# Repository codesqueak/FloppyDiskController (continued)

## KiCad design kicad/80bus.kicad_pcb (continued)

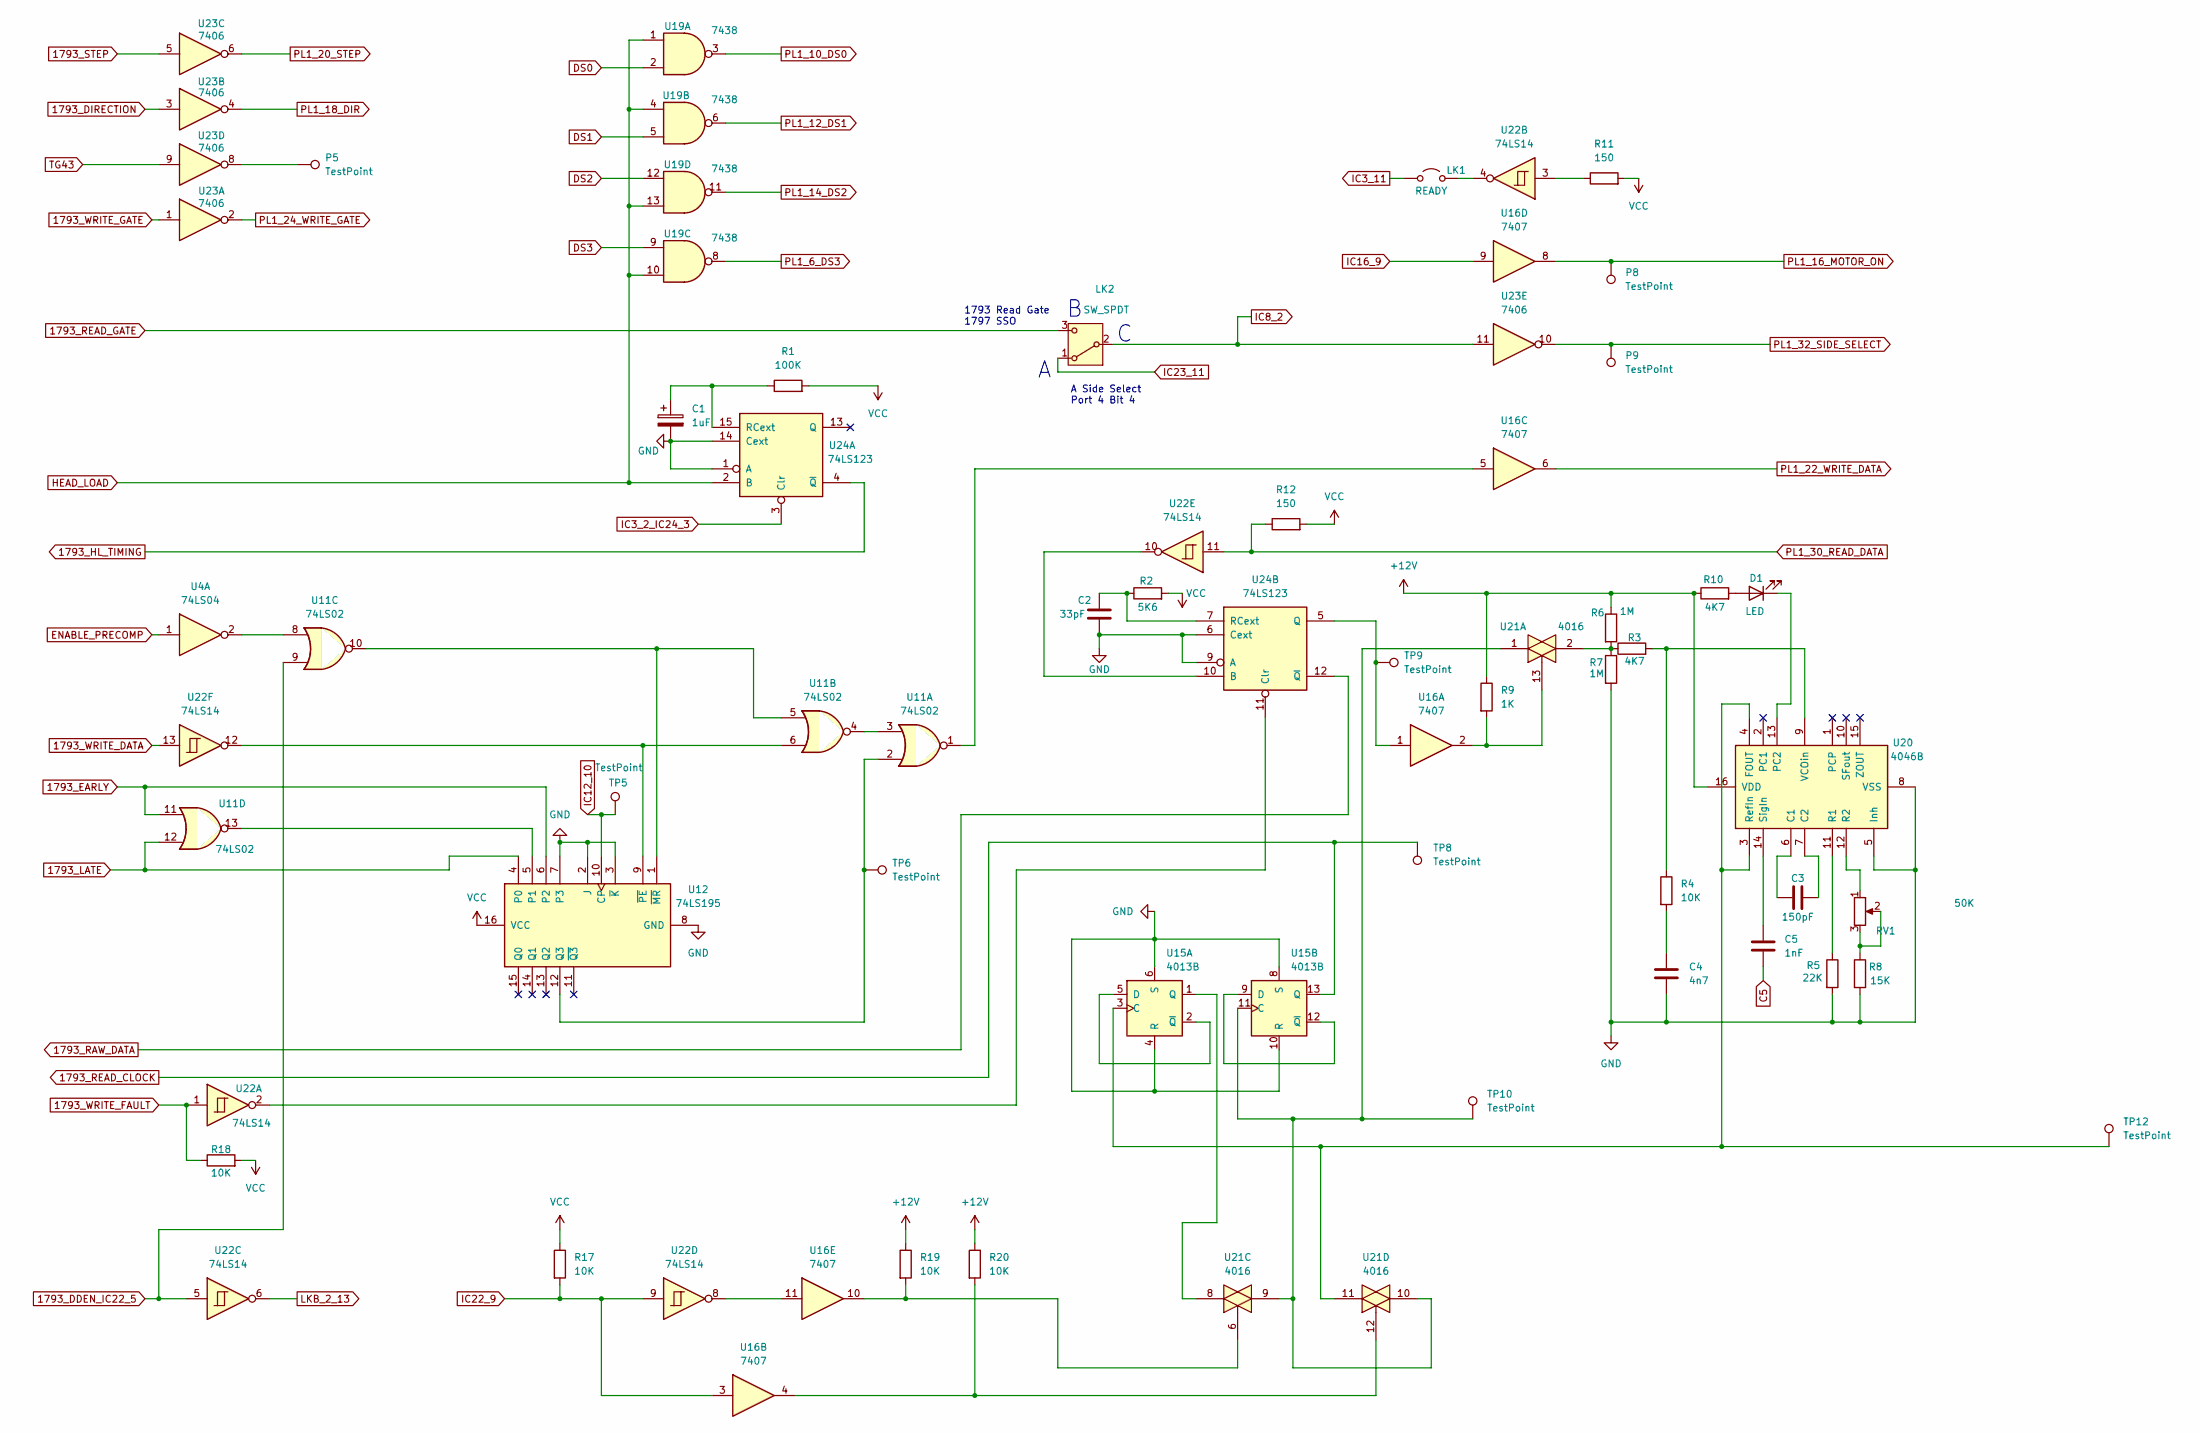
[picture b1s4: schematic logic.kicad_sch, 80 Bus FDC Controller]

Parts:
C1: 1uF; C_Disc_D6.0mm_W4.4mm_P5.00mm
C2: 33pF; C_Disc_D6.0mm_W4.4mm_P5.00mm
C3: 150pF; C_Disc_D6.0mm_W4.4mm_P5.00mm
C4: 4n7; C_Axial_L12.0mm_D6.5mm_P15.00mm_Horizontal
C5: 1nF; C_Disc_D6.0mm_W4.4mm_P5.00mm
D1: LED; LED_D3.0mm
LK1: READY; SW_DIP_SPSTx01_Slide_6.7x4.1mm_W7.62mm_P2.54mm_LowProfile
LK2: SW_SPDT; PinHeader_1x03_P2.54mm_Vertical
P5, P8, P9: TestPoint; TestPoint_THTPad_D1.5mm_Drill0.7mm
R1: 100K; R_Axial_DIN0309_L9.0mm_D3.2mm_P12.70mm_Horizontal
R2: 5K6; R_Axial_DIN0309_L9.0mm_D3.2mm_P12.70mm_Horizontal
R3, R10: 4K7; R_Axial_DIN0309_L9.0mm_D3.2mm_P12.70mm_Horizontal
R4, R17, R18, R19, R20: 10K; R_Axial_DIN0309_L9.0mm_D3.2mm_P12.70mm_Horizontal
R5: 22K; R_Axial_DIN0309_L9.0mm_D3.2mm_P12.70mm_Horizontal
R6, R7: 1M; R_Axial_DIN0309_L9.0mm_D3.2mm_P12.70mm_Horizontal
R8: 15K; R_Axial_DIN0309_L9.0mm_D3.2mm_P12.70mm_Horizontal
R9: 1K; R_Axial_DIN0309_L9.0mm_D3.2mm_P12.70mm_Horizontal
R11, R12: 150; R_Axial_DIN0309_L9.0mm_D3.2mm_P12.70mm_Horizontal
RV1: 50K; Potentiometer_Vishay_43_Horizontal
TP5, TP6, TP8, TP9, TP10, TP12: TestPoint; TestPoint_THTPad_D1.5mm_Drill0.7mm
U4: 74LS04; DIP-14_W7.62mm_Socket
U11: 74LS02; DIP-14_W7.62mm_Socket
U12: 74LS195; DIP-16_W7.62mm_Socket
U15: 4013B; DIP-14_W7.62mm_Socket
U16: 7407; DIP-14_W7.62mm_Socket
U19: 7438; DIP-14_W7.62mm_Socket
U20: 4046B; DIP-16_W7.62mm_Socket
U21: 4016; DIP-14_W7.62mm_Socket
U22: 74LS14; DIP-14_W7.62mm_Socket
U23: 7406; DIP-14_W7.62mm_Socket
U24: 74LS123; DIP-16_W7.62mm_Socket

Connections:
1793_DDEN_IC22_5: U11.9, U22.5; also elsewhere on the board
1793_DIRECTION: U23.3; also elsewhere on the board
1793_EARLY: U11.11, U12.6 (P2); also elsewhere on the board
1793_HL_TIMING: U24.4 (~Q); also elsewhere on the board
1793_LATE: U11.12, U12.4 (P0); also elsewhere on the board
1793_RAW_DATA: U24.12 (~Q); also elsewhere on the board
1793_READ_CLOCK: TP8.1, U15.13 (Q); also elsewhere on the board
1793_READ_GATE: LK2.3 (C); also elsewhere on the board
1793_STEP: U23.5; also elsewhere on the board
1793_WRITE_DATA: U22.13; also elsewhere on the board
1793_WRITE_FAULT: R18.1, U22.1; also elsewhere on the board
1793_WRITE_GATE: U23.1; also elsewhere on the board
+12V: R6.1, R9.1, R10.1, R19.1, R20.1, U20.16 (VDD); also elsewhere on the board
C5: C5.2; also elsewhere on the board
DS0: U19.2; also elsewhere on the board
DS1: U19.5; also elsewhere on the board
DS2: U19.12; also elsewhere on the board
DS3: U19.9; also elsewhere on the board
ENABLE_PRECOMP: U4.1; also elsewhere on the board
GND: C1.2, C2.2, C4.2, R5.2, R7.2, R8.2, U12.2 (J), U12.3 (~K), U12.7 (P3), U12.8 (GND), U15.4 (R), U15.6 (S), U15.8 (S), U15.10 (R), U20.5 (Inh), U20.8 (VSS), U24.1 (A), U24.6 (Cext), U24.9 (A), U24.14 (Cext); also elsewhere on the board
HEAD_LOAD: U19.1, U19.4, U19.10, U19.13, U24.2 (B); also elsewhere on the board
IC3_2_IC24_3: U24.3 (Clr); also elsewhere on the board
IC3_11: LK1.1 (A); also elsewhere on the board
IC8_2: LK2.2 (B), U23.11; also elsewhere on the board
IC12_10: TP5.1, U12.10 (CP); also elsewhere on the board
IC16_9: U16.9; also elsewhere on the board
IC22_9: R17.2, U16.3, U22.9; also elsewhere on the board
IC23_11: LK2.1 (A); also elsewhere on the board
LKB_2_13: U22.6; also elsewhere on the board
unnamed: C4.1, R4.2
unnamed: D1.2 (A), R10.2
unnamed: D1.1 (K), U20.13 (PC2)
unnamed: LK1.2 (B), U22.4
unnamed: P5.1, U23.8
unnamed: R3.1, R6.2, R7.1, U21.2
unnamed: R8.1, RV1.2, RV1.3
unnamed: R9.2, U16.2, U21.13
unnamed: R11.1, U22.3
unnamed: R19.2, U16.10, U21.6
unnamed: R20.2, U16.4, U21.12
unnamed: U11.1, U16.5
unnamed: U11.3, U11.4
unnamed: U4.2, U11.8
unnamed: U11.13, U12.5 (P1)
unnamed: TP6.1, U11.2, U12.12 (Q3)
unnamed: U11.5, U11.10, U12.1 (~MR)
unnamed: U11.6, U12.9 (~PE), U22.12
unnamed: TP12.1, U15.3 (C), U20.3 (RefIn), U20.4 (FOUT), U21.11
unnamed: U15.2 (~Q), U15.5 (D)
unnamed: U15.1 (Q), U21.8
unnamed: TP10.1, U15.11 (C), U21.1, U21.9, U21.10
unnamed: U15.9 (D), U15.12 (~Q)
unnamed: U16.11, U22.8
unnamed: C3.1, U20.6 (C1)
unnamed: C3.2, U20.7 (C2)
unnamed: R5.1, U20.11 (R1)
unnamed: RV1.1, U20.12 (R2)
unnamed: C5.1, U20.14 (SigIn)
unnamed: R3.2, R4.1, U20.9 (VCOin)
unnamed: C1.1, R1.1, U24.15 (RCext)
unnamed: U22.10, U24.10 (B)
unnamed: U22.2, U24.11 (Clr)
unnamed: TP9.1, U16.1, U24.5 (Q)
unnamed: C2.1, R2.1, U24.7 (RCext)
PL1_6_DS3: U19.8; also elsewhere on the board
PL1_10_DS0: U19.3; also elsewhere on the board
PL1_12_DS1: U19.6; also elsewhere on the board
PL1_14_DS2: U19.11; also elsewhere on the board
PL1_16_MOTOR_ON: P8.1, U16.8; also elsewhere on the board
PL1_18_DIR: U23.4; also elsewhere on the board
PL1_20_STEP: U23.6; also elsewhere on the board
PL1_22_WRITE_DATA: U16.6; also elsewhere on the board
PL1_24_WRITE_GATE: U23.2; also elsewhere on the board
PL1_30_READ_DATA: R12.1, U22.11; also elsewhere on the board
PL1_32_SIDE_SELECT: P9.1, U23.10; also elsewhere on the board
TG43: U23.9; also elsewhere on the board
VCC: R1.2, R2.2, R11.2, R12.2, R17.1, R18.2, U12.16 (VCC); also elsewhere on the board

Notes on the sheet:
1793 Read Gate 1797 SSO
A Side Select Port 4 Bit 4

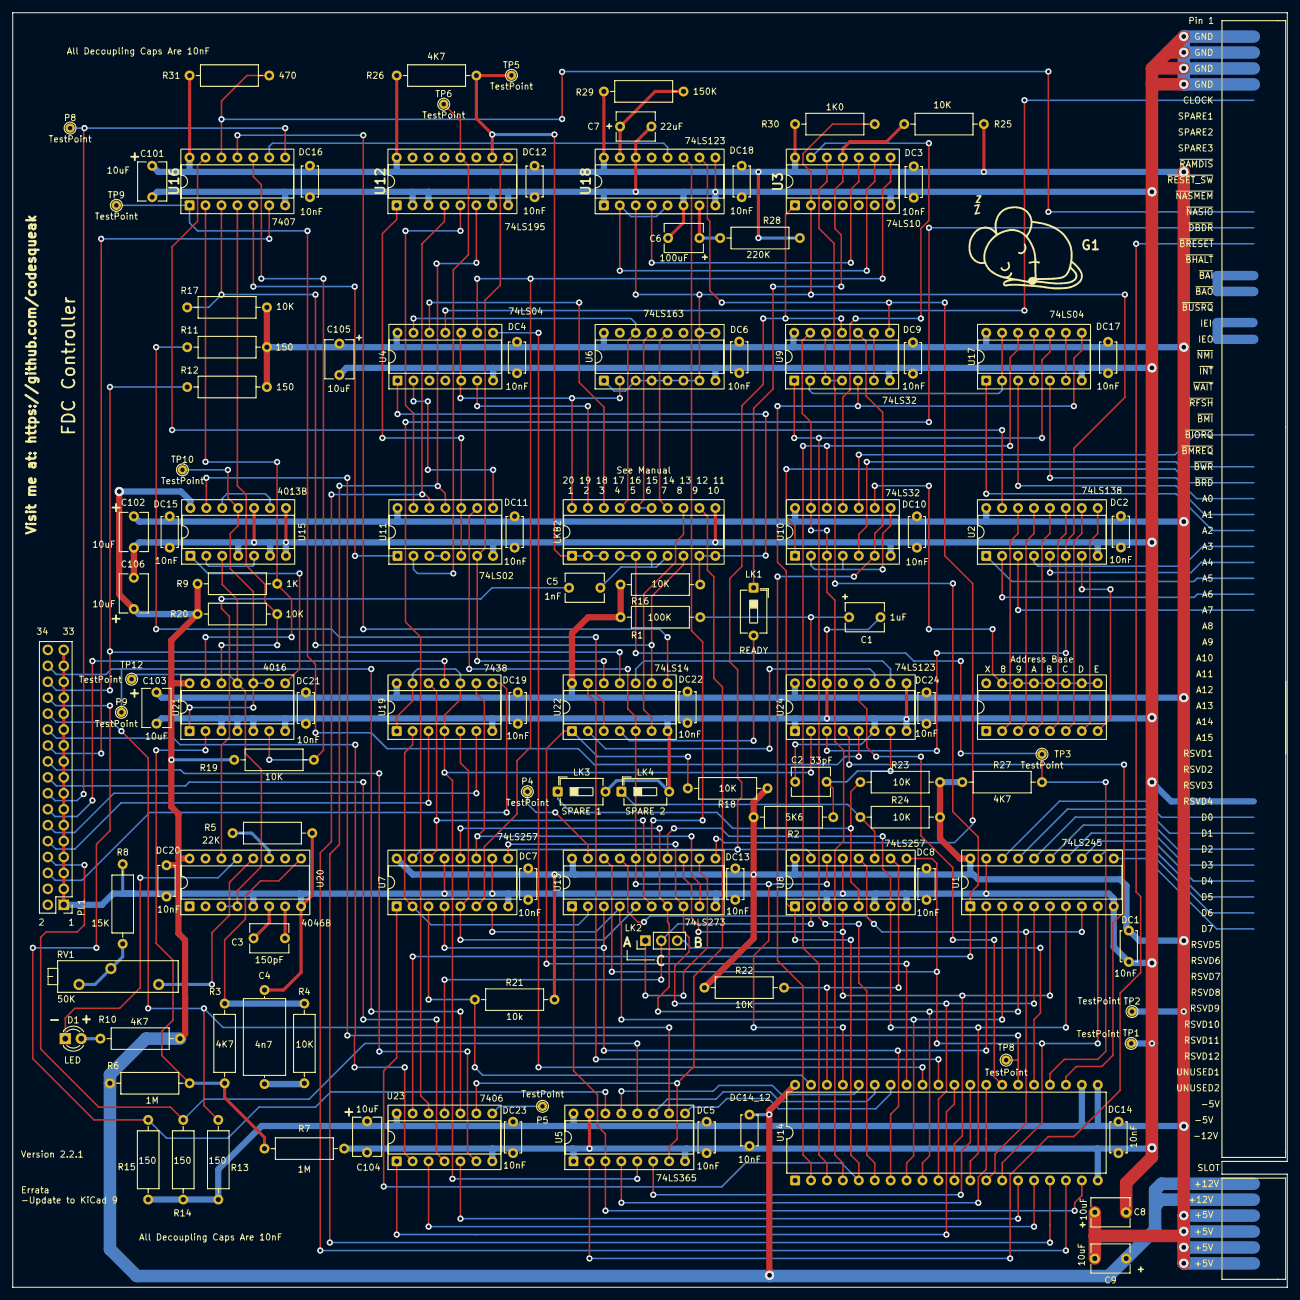
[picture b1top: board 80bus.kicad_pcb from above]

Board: 2 copper layers, 203.2 x 203.2 mm, 120 parts (1 on the bottom side), 162 nets.

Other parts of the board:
G1: LOGO; sleepymouse_small
G001: LOGO; qr-code

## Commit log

2023-07-04 Initial file drop
2023-07-04 Minor tweaks
2023-07-15 Update docs
2023-07-15 More docs
2023-07-15 Remove docx file
2025-02-09 kicad8
2025-03-30 Document update / Kikad 9
2025-04-06 Version update
